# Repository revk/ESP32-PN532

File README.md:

# ESP32-PN532

Now at [Codeberg](https://codeberg.org/RevK/ESP32-PN532)

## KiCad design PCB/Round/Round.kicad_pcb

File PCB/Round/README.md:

# Round

These files are for use in [KiCad](https://www.kicad.org).

## Trademark

This is an open source project, but bear in mind you cannot sell boards bearing the Andrews & Arnold Ltd name, the A&A logo, the registered trademark AJK logo, or the GS1 allocated EANs assigned to Andrews & Arnold Ltd.

## Images

*Auto generated 2025-08-22T10:13:34*

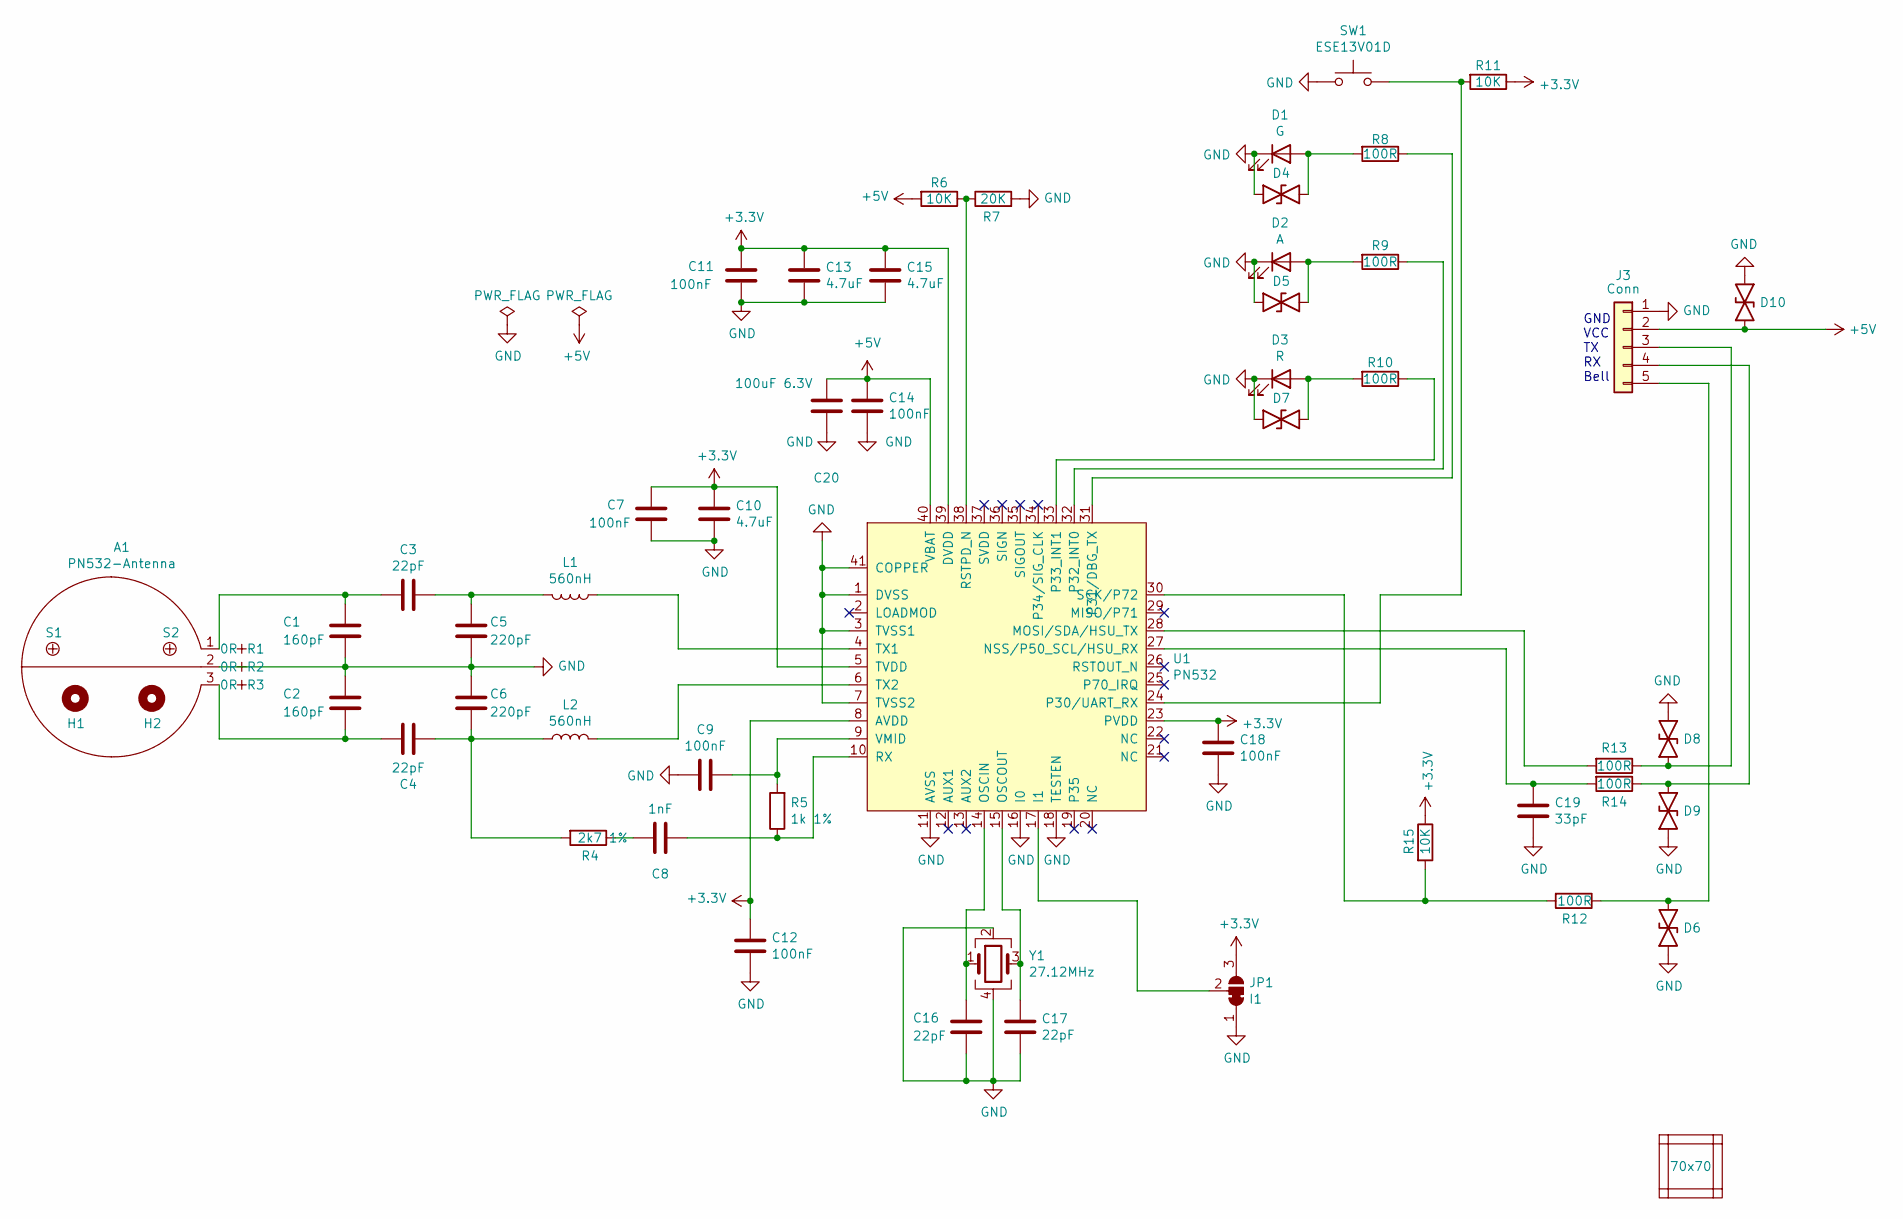
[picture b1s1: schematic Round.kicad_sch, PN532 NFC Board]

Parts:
A1: PN532-Antenna; PN532-Antenna6
C1, C2: 160pF; C_0603
C3, C4: 22pF; C_0603; Part No 0603N220F500CT
C5, C6: 220pF; C_0603; Part No 0603-220pF-50V
C7, C9, C11, C12, C14, C18: 100nF; C_0603; Part No 0603-100nF-25V
C8: 1nF; C_0603; Part No VJ0603A102GXAPW1BC
C10, C13, C15: 4.7uF; C_0603; Part No 0603-4.7uF-10V
C16, C17: 22pF; C_0603; Part No 0603-22pF-50V
C19: 33pF; C_0603; Part No 0603-33pF-50V
C20: 100uF 6.3V; C_1206
D1: G; LED_1206_Rev_Square; Part No 156120VS75300
D2: A; LED_1206_Rev_Square; Part No 156120YS75300
D3: R; LED_1206_Rev_Square; Part No 156120RS75300
D4, D5, D6, D7, D8, D9, D10: DFN1006-2L; MPN C5137770
H1, H2: MountingHole; MountingHole_4mm
J3: Conn; PinHeader_1x05_P2.54mm_Vertical_SMD_Pin1Left; MPN C2883802
JP1: I1; SolderJumper3
L1, L2: 560nH; L_1008_2520Metric; Part No LQW2UASR56G00L
PCB1: 70x70; PCB7070
R1, R3: 0R; R_0603_; MPN 0603
R2: 0R; R_0805_; MPN C17477
R4: 2k7 1%; R_0603; MPN C114612
R5: 1k 1%; R_0603; Part No CRCW06031K00FKEAC
R6, R11, R15: 10K; R_0603; MPN C25804
R7: 20K; R_0603; MPN C4184
R8, R9, R10, R13, R14: 100R; R_0603; MPN C22775
R12: 100R; R_0603; MPN 0603-100R
S1, S2: Screw
SW1: ESE13V01D; ESE13; Part No ESE13V01D
U1: PN532; QFN-40-1EP_6x6mm_P0.5mm_EP4.6x4.6mm; MPN C28925
V1, V2, V3, V4: VCUT70
Y1: 27.12MHz; Crystal-3.2x2.5; Part No ABM81-27.120MHZ-10-B1U-T3

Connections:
+3.3V: C7.1, C10.1, C11.1, C12.1, C13.1, C15.1, C18.1, JP1.3 (B), R11.1, R15.1, U1.5 (TVDD), U1.8 (AVDD), U1.23 (PVDD), U1.39 (DVDD)
+5V: C14.1, C20.2, D10.2, J3.2, R6.2, U1.40 (VBAT)
GND: A1.2, C1.2, C2.1, C5.1, C6.1, C7.2, C9.2, C10.2, C11.2, C12.2, C13.2, C14.2, C15.2, C16.2, C17.2, C18.2, C19.2, C20.1, D1.1 (K), D2.1 (K), D3.1 (K), D4.2, D5.2, D6.2, D7.2, D8.1, D9.2, D10.1, J3.1, JP1.1 (A), R7.2, SW1.1, U1.1 (DVSS), U1.3 (TVSS1), U1.7 (TVSS2), U1.11 (AVSS), U1.16 (I0), U1.18 (TESTEN), U1.41 (COPPER), Y1.2, Y1.4
unnamed: A1.1, C1.1, C3.2
unnamed: A1.3, C2.2, C4.1
unnamed: C3.1, C5.2, L1.2
unnamed: C4.2, C6.2, L2.1, R4.2
unnamed: C8.2, R4.1
unnamed: D1.2 (A), D4.1, R8.2
unnamed: D2.2 (A), D5.1, R9.2
unnamed: D3.2 (A), D7.1, R10.2
unnamed: D8.2, J3.3, R13.1
unnamed: D9.1, J3.4, R14.1
unnamed: D6.1, J3.5, R12.1
unnamed: JP1.2 (C), U1.17 (I1)
unnamed: R13.2, U1.28 (MOSI/SDA/HSU_TX)
unnamed: C19.1, R14.2, U1.27 (NSS/P50_SCL/HSU_RX)
unnamed: C16.1, U1.14 (OSCIN), Y1.1
unnamed: C17.1, U1.15 (OSCOUT), Y1.3
unnamed: R11.2, SW1.2, U1.24 (P30/UART_RX)
unnamed: R8.1, U1.31 (P31/DBG_TX)
unnamed: R9.1, U1.32 (P32_INT0)
unnamed: R10.1, U1.33 (P33_INT1)
unnamed: R6.1, R7.1, U1.38 (RSTPD_N)
unnamed: C8.1, R5.1, U1.10 (RX)
unnamed: R12.2, R15.2, U1.30 (SCK/P72)
unnamed: L1.1, U1.4 (TX1)
unnamed: L2.2, U1.6 (TX2)
unnamed: C9.1, R5.2, U1.9 (VMID)

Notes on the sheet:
GND VCC TX RX Bell

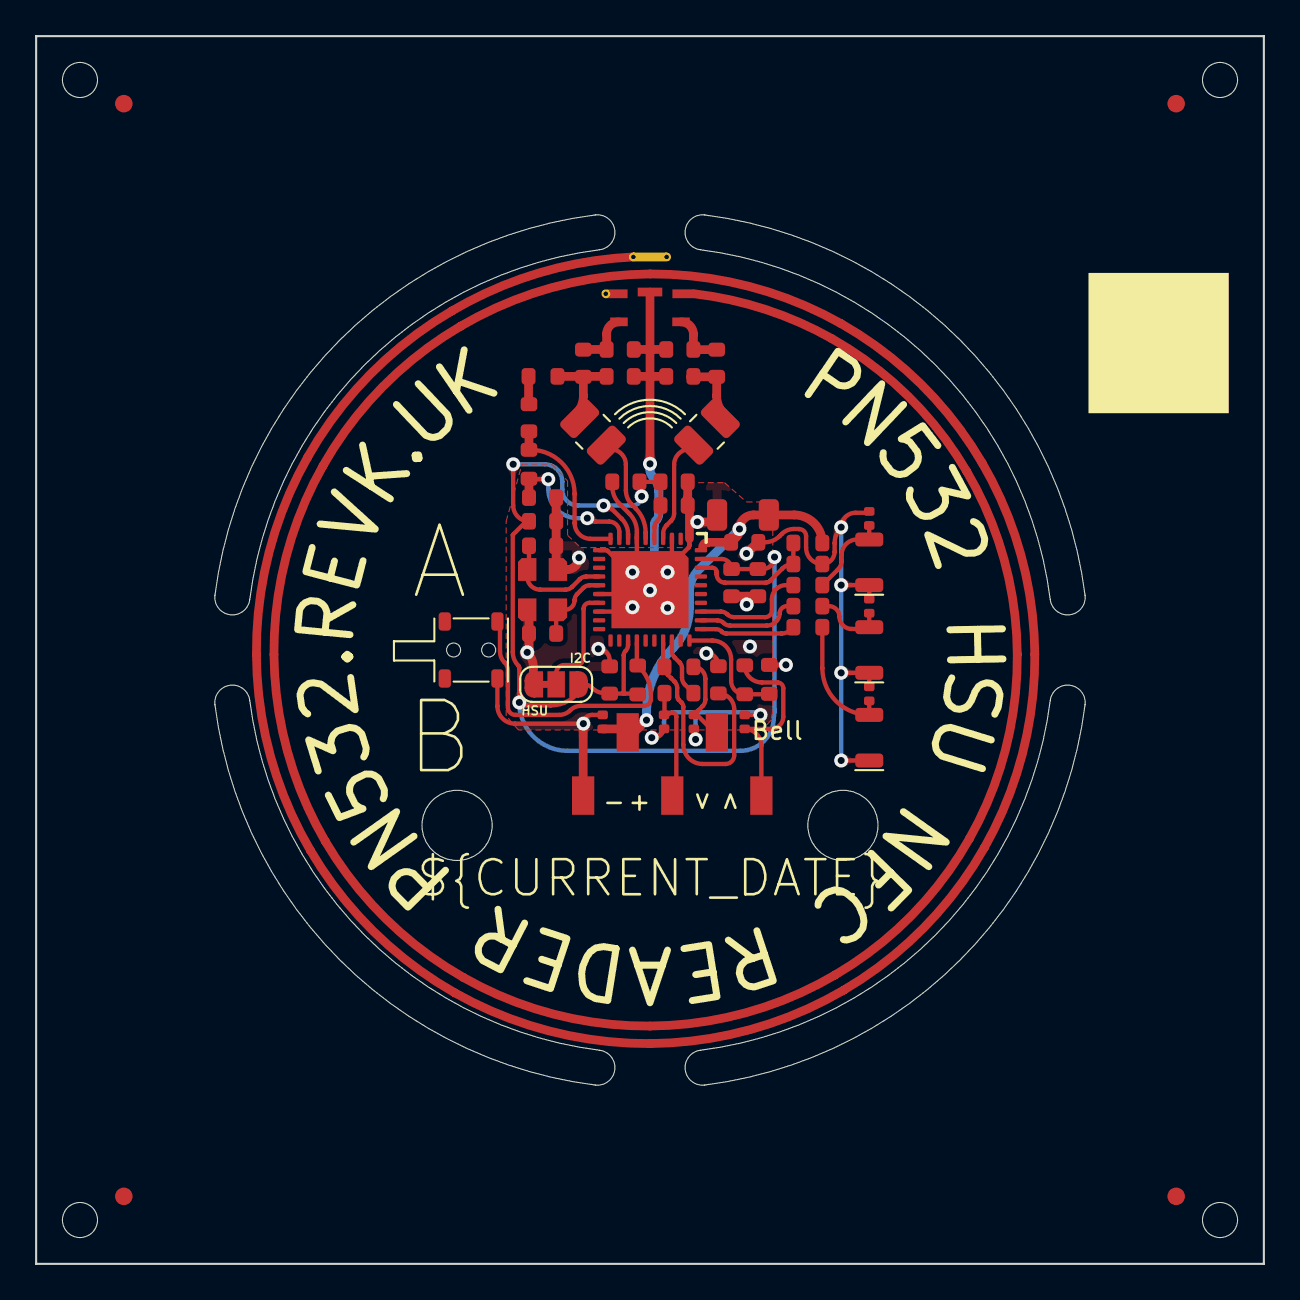
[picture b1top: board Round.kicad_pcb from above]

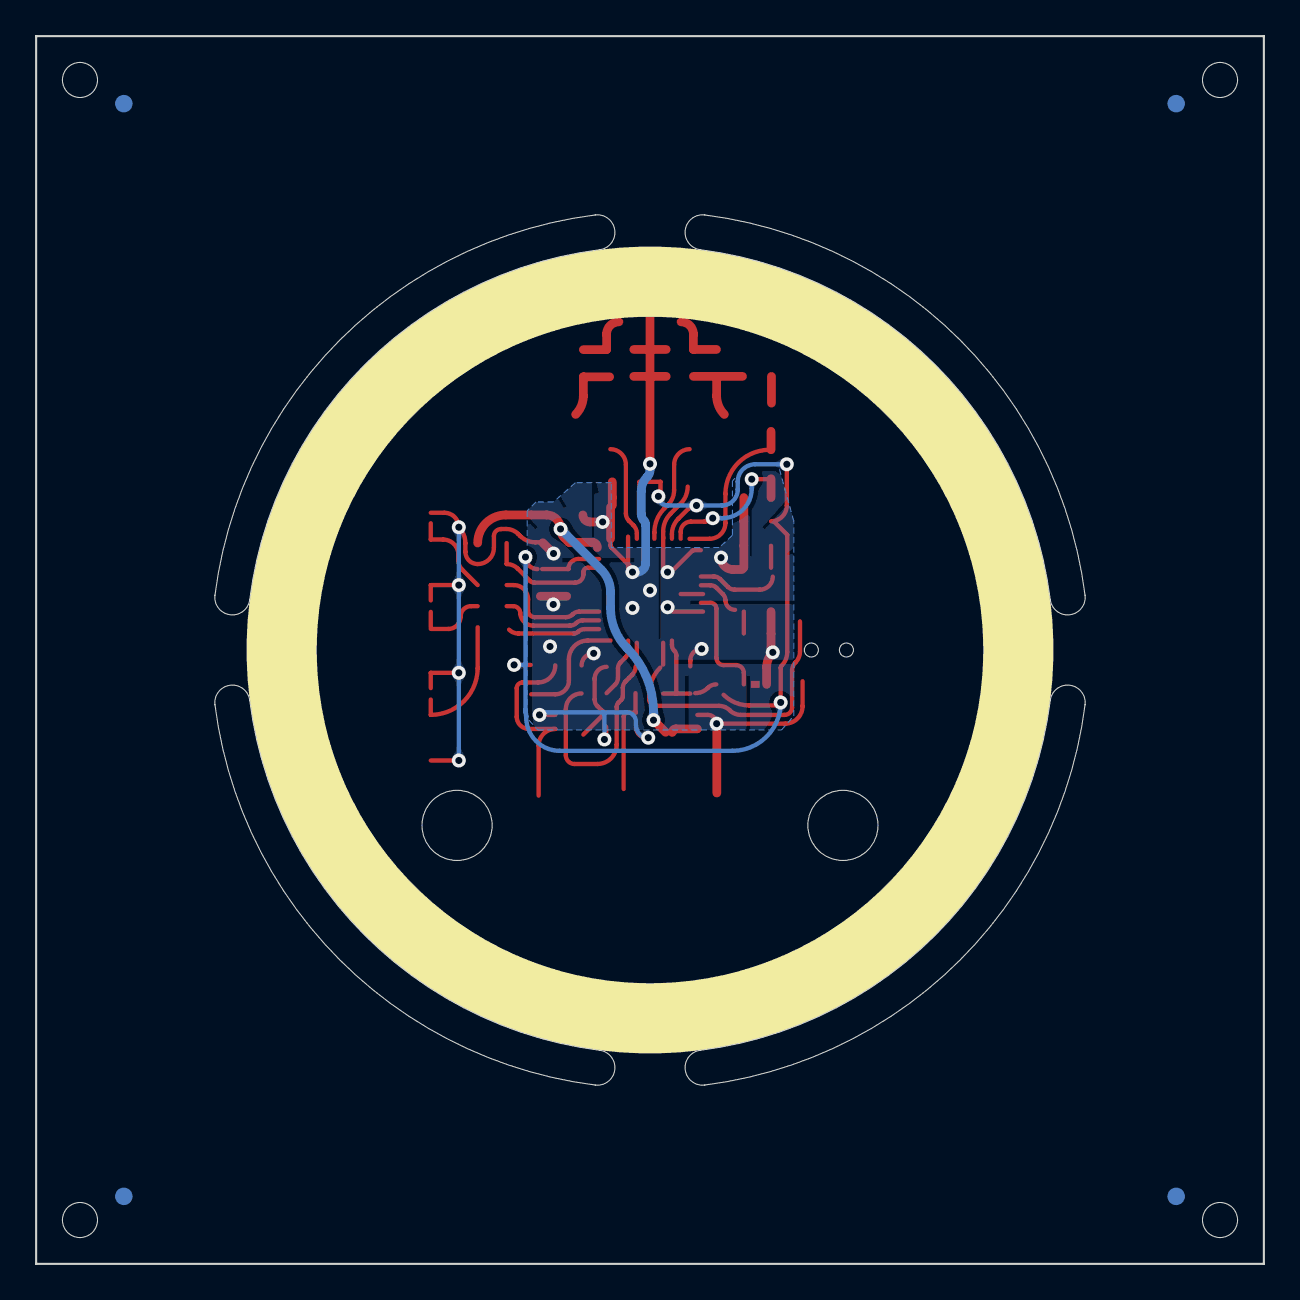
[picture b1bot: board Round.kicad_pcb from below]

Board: 2 copper layers, 70.0 x 70.0 mm, 62 parts (4 on the bottom side), 29 nets.

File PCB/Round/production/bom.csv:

Designator,Footprint,Quantity,Value,LCSC Part #
"C1, C2",C_0603,2,160pF,
"C10, C13, C15",C_0603,3,4.7uF,
"C11, C12, C14, C18, C7, C9",C_0603,6,100nF,
"C16, C17, C3, C4",C_0603,4,22pF,
C19,C_0603,1,33pF,
C20,C_1206,1,100uF 6.3V,
"C5, C6",C_0603,2,220pF,
C8,C_0603,1,1nF,
D1,LED_1206_Rev_Square,1,G,C157737
"D10, D4, D5, D6, D7, D8, D9",DFN1006-2L,7,~,C5137770
D2,LED_1206_Rev_Square,1,A,C125108
D3,LED_1206_Rev_Square,1,R,C125107
J3,PinHeader_1x05_P2.54mm_Vertical_SMD_Pin1Left,1,Conn,C2883802
"L1, L2",1008,2,560nH,C75639
"R1, R3",R_0603_,2,0R,0603
"R10, R13, R14, R8, R9",R_0603,5,100R,C22775
"R11, R15, R6",R_0603,3,10K,C25804
R12,R_0603,1,100R,0603-100R
R2,R_0805_,1,0R,C17477
R4,R_0603,1,2k7 1%,C114612
R5,R_0603,1,1k 1%,C22548
R7,R_0603,1,20K,C4184
SW1,ESE13,1,ESE13V01D,
U1,QFN-40-1EP_6x6mm_P0.5mm_EP4.6x4.6mm,1,PN532,C28925
Y1,Crystal-3.2x2.5,1,27.12MHz,C70591

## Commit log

2021-04-20 Better GPIO
2021-04-21 PCB design
2021-04-21 Update README.md
    PCB added
2021-04-21 More tinkering
2021-04-21 As ordered 2021-04-21
2021-04-22 Swapped LEDs and tweaked track for Rx side
2021-04-23 Tweak
2021-04-23 Documentation
2021-04-23 Test code
2021-04-23 Simpler
2021-04-23 Correct PCB edge
2021-04-24 Moved Tamper to top, make easier for mounting screws in 3D case base.
2021-04-24 Added external tamper/button header
2021-04-24 Started case
2021-04-24 Ooops
2021-04-24 Tweaks
2021-04-25 Minor tweaks :-)
2021-04-25 Mention 3D
2021-04-25 Correct tamper height, and spox placement
2021-04-25 Added links to mouser for connectors
2021-04-25 Tidy some tracks
2021-04-25 Lip, and screw fix
2021-04-25 Messed up the lip, D'Oh
2021-04-25 Fix base
2021-04-25 Cable entry narrower and lock in the SPOX when lid in place
2021-04-25 OK try that again, locking in connector
2021-04-25 More tweaks
2021-04-25 Tweaked tracks, yet again.
2021-04-25 Update README.md
    Latest image
2021-04-25 Reworked milli-grid and made button separate to tamper
2021-04-25 Tidy
2021-04-25 Test
2021-04-25 Silk screen tweak
2021-04-26 D'Oh
2021-04-26 Turned LEDs sideways so could be fitted at right angles easily
2021-04-27 Cleaner holes
2021-04-27 Tidy tracks
2021-04-27 Values
2021-04-27 Correct value
2021-04-28 Reworked using 0603
2021-04-28 Shorter loop
2021-04-28 As ordered
2021-04-28 Case for new design
2021-04-28 Revised to add vias for antenna testing (after PCB issue today)
2021-04-28 Silk screen
2021-04-29 Minor tidy and adjust case
2021-04-29 Current 3D model
2021-04-29 Reworked for 9mm corners
2021-04-29 As ordered NFCV4
2021-04-30 Some example STL files
2021-04-30 Correct paste
2021-04-30 Moved resistors to be definitely clear of vertical SPOX
2021-04-30 Adjusting connector holes
2021-05-01 Mark test points
2021-05-01 Proper test points now on schematic and PCB layout for antenna tuning.
2021-05-01 Cleaner tracks
2021-05-04 Added JP1 link to allow I2C
2021-05-04 Moved vias from under pads as better for use with solder paste. Added date to solder paste stencil
2021-05-05 Some silk screen tweaks
2021-05-05 Tweak footprint
2021-05-05 brighter green
2021-05-06 footprint name fix
2021-05-06 Allow SMD tamper switch (pads)
2021-05-06 Adjusted tamper
2021-05-06 Moved around tamper, as will not start with P35 grounded, grrr.
2021-05-06 Silk
2021-05-06 Back to antenna 1
2021-05-07 Tidy fab
2021-05-07 Case for antenna1
2021-05-08 Tidy fab layer
2021-05-08 Back to later antenna as it is better, waiting on RF work to fine tune
2021-05-08 Change to 1206 pads for inductor
2021-05-08 Tidy a bit with smaller ground plane
2021-05-08 More space around inductor.
2021-05-08 Some advice re RF leading to tweaks to ground plane.
2021-05-08 Complete re-layout (needs 3D case changes still)
2021-05-08 Plot
2021-05-08 Added dimensions
2021-05-09 Minor updates, moved bell, 3D case updated
2021-05-09 Logo
2021-05-09 More tidying
2021-05-09 More tweaks - do they ever end?
2021-05-09 Update docs
2021-05-09 Reworked.
2021-05-10 Double Cap pads to improve tuning options, and large inductor pad
2021-05-11 Diagonal inductors for the win...
2021-05-11 Paste update
2021-05-12 ESD on bell, and tidy
2021-05-12 Protection diodes for ESD
2021-05-12 Minor final tweaks
2021-05-12 dates
2021-05-13 Moved by 0.1mm to line up, D'Oh
2021-05-13 Tidy up diode positioning and add 33pF on rx
2021-05-13 Update board
2021-05-13 Documentation update
2021-05-14 Remade
2021-05-14 Correct LEDs
2021-05-14 Fix I/O set up
2021-05-15 Larger test pads
2021-05-16 Cleaner start maybe
2021-05-17 Final tidy for order
2021-05-18 Updated logo on copper
2021-05-18 A&A logo
2021-05-18 Fix 3D
2021-05-18 200pF
2021-05-18 100ms
2021-05-18 Allow a tad more
2021-05-18 200ms
2021-05-19 Try change timings
2021-05-19 Not that
2021-05-19 No help
2021-05-19 Adjust timings
2021-05-20 Holes for bell pins fixed
2021-05-31 Note
2021-06-01 Minor tweak around LEDs
2021-06-01 Slot for reverse LED mounting option
2021-06-02 Fix notes
2021-06-03 Changed to 40mm x 40mm x 0.8mm design, seems better.
2021-06-03 Update drawings for new PCB
2021-06-03 Tidy drawing
2021-06-03 New 3D
2021-06-03 Tamper tweak
2021-06-07 Debug Kconfig
2021-06-07 Should that be necessary?
2021-06-07 Clarify
2021-06-07 Flash stuff makes it take longer?
2021-06-07 No help - flash can proper stall things
2021-06-10 Silly error
2021-06-10 Closer tamper
2021-06-10 Tweak tamper
2021-06-13 Was causing leak
2021-06-13 Not the leak, so where is it?
2021-06-13 Tamper clearance
2021-06-13 Leak
2021-06-17 Better pads for solder paste
2021-06-28 release and deselect
2021-06-28 typo
2021-06-29 Debug
2021-06-29 Silly
2021-06-29 Tidy name
2021-06-29 Wording
2021-06-30 Logging error
2021-07-06 Footprint
2021-07-09 Solder paste
2021-07-09 Value change
2021-07-10 Soldaer paste
2021-07-24 Changed to just SMD LEDs
2021-07-25 Screws
2021-08-26 Solder stencil adjust
2021-10-09 For some reason longer timeouts needed now
2021-11-03 Tweaked artwork / logo / LEDs
2021-12-29 Kicad 6
2021-12-30 Gerenal KIcad 6 related tidy up
2021-12-31 Reworked slightly to ensure 0R in BOM, and passing DRC cleanly under Kicad 6
2021-12-31 Cleaner hidden components
2021-12-31 Pretty
2021-12-31 More minor tweaks
2021-12-31 Eyebrows?
2022-01-01 Part numbers
2022-01-01 Tidy up
2022-01-01 Fabrication files
2022-01-01 All new curvy tracks and changed layout for cleaner Rx path
2022-01-01 BOM tidy
2022-01-01 Pos file fixes
2022-01-01 More bom/pos tidy
2022-01-01 Fix bad footprint import
2022-01-02 Mostly cosmetic changes and a few track tweaks
2022-01-02 Cosmetic
2022-01-02 Never ending tinkering
2022-01-02 More cut down.
2022-01-03 Cleaner up BOM
2022-01-03 Reverse mount LEDs
2022-01-04 Cleanup BOM more
2022-01-05 As ordered from PCB Train today
2022-01-06 Changed URL
2022-01-06 Minor change
2022-01-17 Minor tweaks, all looking good.
2022-02-02 Idiot
2022-02-09 Tidy plated holes
2022-02-09 Adjust LED slightly
2022-02-18 QR + date, and tweaks
2022-02-18 Update artwork
2022-06-18 Tweak case designs
2022-06-18 Chamfer
2022-06-18 Handle reverse LEDs
2022-06-18 Tamper height adjust
2022-06-18 Bugger tamper to allow for placement.
2022-06-21 New round circuit (unfinshed)
2022-06-22 New antenna design
2022-06-22 Better antennna
2022-06-23 Tweak screw holes, and tidy round PCB
2022-06-29 Tidy up and new case
2022-06-29 Better images
2022-06-29 Library update
2022-06-29 Cleaner cuts in copper
2022-06-30 Round case
2022-06-30 Better screw holes
2022-06-30 Tweak access
2022-07-04 Tamper needed to be tighter
2022-07-08 Tamper
2022-07-08 Slight clean up
2022-07-08 Cleaner positioning
2022-07-12 Tidy up LEDs, etc.
2022-07-25 Definite pin reset - probably not needed, but makes sure
2022-08-05 Proper tamper switch
2022-08-05 Revised layout (tamper)
2022-08-05 Changed to new tamper
2022-08-06 Changed back.
2022-08-15 zip files
2022-08-22 Made bell part of connector, optional 4 or 5 way, and removed connector for tamper as not protected and good tamper switch now.
2022-08-23 Revised connector
2022-12-31 driver
2022-12-31 v5.0 uart init
2023-01-11 Production files - not finished
2023-01-12 Production nearly ready - may have to change to square LEDs.
2023-01-13 production for LEDs as well
2023-01-20 Origin
2023-03-22 Tweak SS
2023-04-24 Tweaked for latest PCB
2023-06-22 popt changes
2023-06-30 Panel
2023-07-01 --panel
2023-07-01 Case
2023-07-01 Revised case
2023-07-02 UART_HW_FIFO_LEN
2023-07-03 Cleaner edge
2023-08-18 Warnings
2023-12-21 Tidy and new ESP diodes
2024-01-18 Baud setting
2024-01-18 rate change
2024-01-19 Baud rate change logic
2024-01-23 Less space, as before
2024-05-12 5.2.1 has some checks that broke this
2024-05-12 Try that
2024-12-11 Playing with antenna
2024-12-11 Started on inverted antenna
2024-12-11 Make external antenna
2024-12-11 Indent
2024-12-11 External
2024-12-11 Exclude
2024-12-12 Pads
2025-01-19 Not working yet
2025-01-19 Working on new images
2025-01-19 Images
2025-01-23 PCB Update
2025-08-09 Re-do case
2025-08-10 Slight tweak
2025-08-17 Faceplate
2025-08-17 Plate 90 degrees
2025-08-20 Change part
2025-08-21 Screw adjust
2025-08-22 Changed locking holes
2025-08-22 Fix angle and plate thickness
2025-08-22 Rounder corners to match back box
2025-08-23 Same thickness
2025-08-23 Arg, fix position, again
2025-08-24 Avoid silly mistake next time
2025-09-03 Testing
2025-09-03 Updated case logic from PCB
2025-11-09 Not sure
2025-11-09 Out of date
2025-11-09 Start on local test code
2025-11-09 Started testing
2025-11-09 Fis ifdef
2025-11-09 OK now ready for target functions
2025-11-09 More renders
2025-11-10 atq/sak
2025-11-10 pn532_type
2025-11-10 Tweak MxRtyATR
2025-11-10 Progress
2025-11-10 pn532_txrx
2025-11-11 Finally answering NDEF in test
2026-02-13 submodule
